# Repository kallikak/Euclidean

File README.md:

# Euclidean

This is the repository for the code for The EUCLIDEAN synthesiser. The main sketch is in the Euclid folder, but to build it some small changes need to be made to the Teensyduino environment.

- In order to use the Ensemble effect, the two files effect_ensemble.c and effect_ensemble.h need to be added to the audio library, and effect_ensemble.h added to the Audio.h header.

- The ST7735_t3 library is used for the LCD. The fonts I use are in the Fonts folder, and need to be added to the library if not already present.

- The other libraries needed are:
  - IntervalTimer
  - Bounce2mcp
  - Adafruit_MCP23017
  - MIDI
  - USBHost_t36
  - SD_t3.h
  - ADC (only needed if for some reason the pots are particularly noisy/jittery)

- You cannot use the default Audio Library GUI with the code from Euclid.ino because it doesn't recognise AudioEffectEnsemble.  The easiest change is to make it AudioEffectChorus  instead (and change AudioConnection patchCord60(chorus, 1, effectmixR, 1) to AudioConnection patchCord60(chorus, 0, effectmixR, 1)), but remember to change it back if you make changes and want to update.

- Compile with USB type set to Serial + MIDI + Audio, and no harm overclocking to 816MHz.

- Prebuilt hex files are provided for both Teensy 4.0 and Teensy 4.1.

A User Guide for the synthesizer is here: http://thewessens.net/Euclid/Docs/User/euclideaninfo.html

A Build Guide for the kit is here: http://thewessens.net/Euclid/Docs/Build/euclideanbuild.html

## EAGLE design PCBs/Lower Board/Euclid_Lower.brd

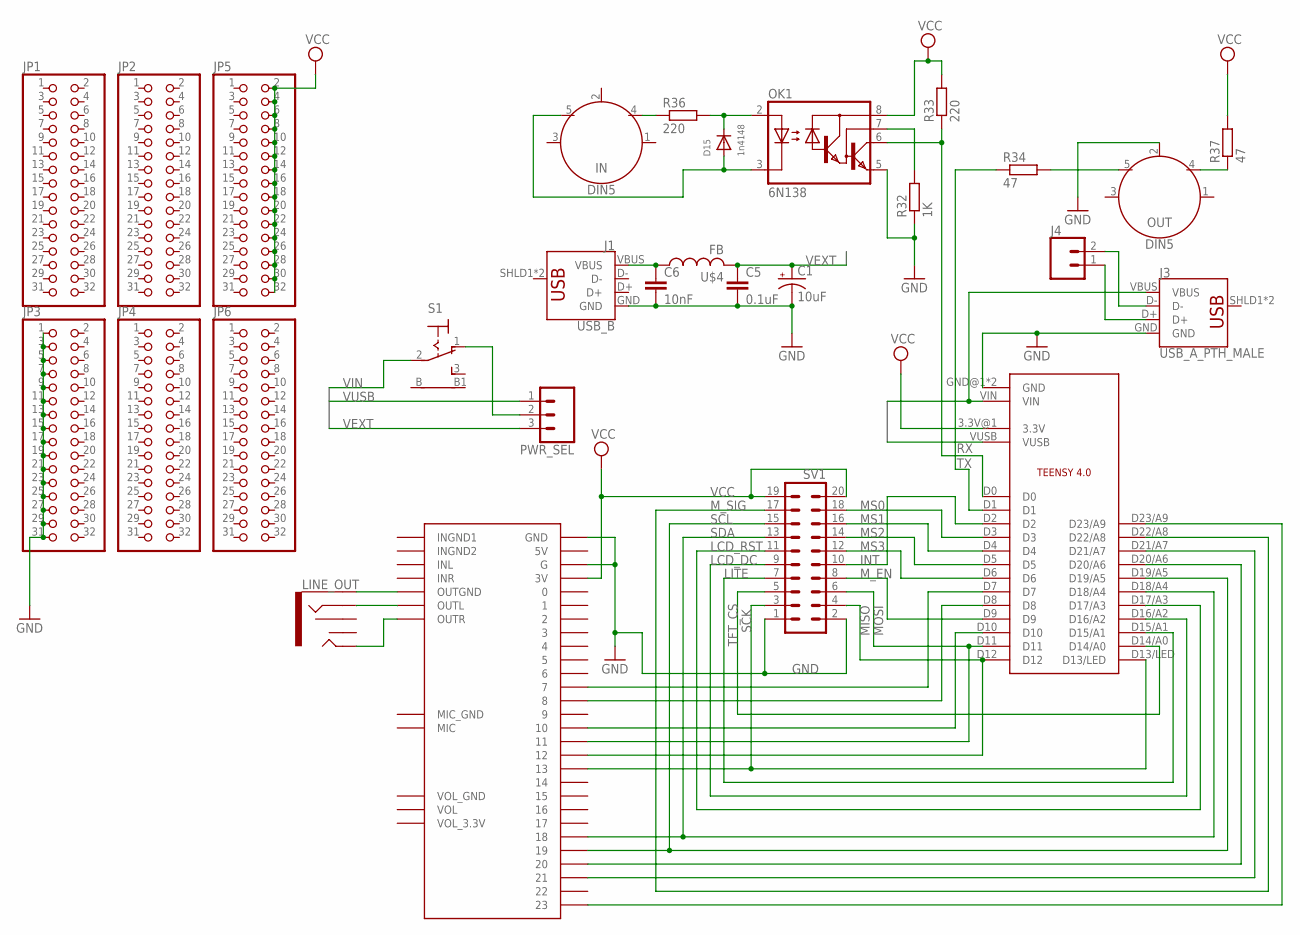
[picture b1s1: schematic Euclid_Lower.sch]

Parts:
C1: 10uF; TT5D6
C5: 0.1uF; C025-025X050
C6: 10nF; C025-025X050
D15: 1n4148; DO-1N4148
IN: DIN5; DIN5-RA-PTH
J1: USB_B; USB-B-NO-OVERHANG
J3: USB_A_PTH_MALE; USB-A-H
J4: CONN_02; 1X02
JP1, JP2, JP3, JP4, JP5, JP6: PINHD-2X16; 2X16
LINE_OUT: AUDIO_JACK_3.5MM_KIT; AUDIO-JACK-KIT
OK1: 6N138; DIL08
OUT: DIN5; DIN5-RA-PTH
PWR_SEL: 455-1750-1-ND; 1X03
R32: 1K; 0207/10
R33, R36: 220; 0207/10
R34, R37: 47; 0207/10
S1: 9070-1W
SV1: MA10-2
U$1: TEENSY4.0_SIMPLE
U$3: AUDIOSHIELD
U$4: FB

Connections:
D+: J3.D+, J4.1
D-: J3.D-, J4.2
GND: C1.-, C5.2, C6.2, J1.GND, J3.GND, JP3.1, JP3.3, JP3.5, JP3.7, JP3.9, JP3.11, JP3.13, JP3.15, JP3.17, JP3.19, JP3.21, JP3.23, JP3.25, JP3.27, JP3.29, JP3.31, OK1.5 (GND), OUT.2, R32.1, SV1.1, SV1.2, U$1.GND@1 (GND), U$1.GND@2 (GND), U$3.G, U$3.GND
INT: SV1.10, U$1.D2
LCD_DC: SV1.9, U$1.D16/A2
LCD_RST: SV1.11, U$1.D17/A3
LITE: SV1.7, U$1.D15/A1
MISO: SV1.4, U$1.D12, U$3.12
MOSI: SV1.6, U$1.D11, U$3.11
MS0: SV1.18, U$1.D3
MS1: SV1.16, U$1.D4
MS2: SV1.14, U$1.D5
MS3: SV1.12, U$1.D6
M_EN: SV1.8, U$1.D9
M_SIG: SV1.17, U$1.D22/A8
unnamed: U$1.D20/A6, U$3.20
unnamed: U$1.D21/A7, U$3.21
unnamed: U$1.D23/A9, U$3.23
unnamed: U$1.D10, U$3.10
unnamed: U$1.D7, U$3.7
unnamed: U$1.D8, U$3.8
unnamed: PWR_SEL.2, S1.1 (O)
unnamed: OUT.5, R34.2
unnamed: OK1.7 (VB), R32.2
unnamed: D15.A, IN.5, OK1.3 (C)
unnamed: D15.C, OK1.2 (A), R36.2
unnamed: IN.4, R36.1
unnamed: LINE_OUT.SLEEVE, U$3.OUTGND
unnamed: C6.1, J1.VBUS, U$4.P$1 (1)
unnamed: OUT.4, R37.1
unnamed: LINE_OUT.RING, U$3.OUTL
unnamed: LINE_OUT.TIP, U$3.OUTR
RX: OK1.6 (VO), R33.1, U$1.D0
SCK: SV1.3, U$1.D13/LED, U$3.13
SCL: SV1.15, U$1.D19/A5, U$3.19
SDA: SV1.13, U$1.D18/A4, U$3.18
TFT_CS: SV1.5, U$1.D14/A0
TX: R34.1, U$1.D1
VCC: JP5.2, JP5.4, JP5.6, JP5.8, JP5.10, JP5.12, JP5.14, JP5.16, JP5.18, JP5.20, JP5.22, JP5.24, JP5.26, JP5.28, JP5.30, JP5.32, OK1.8 (VCC), R33.2, R37.2, SV1.19, SV1.20, U$1.3.3V@1 (3.3V), U$3.3V
VEXT: C1.+, C5.1, PWR_SEL.3, U$4.P$2 (2)
VIN: J3.VBUS, S1.2, U$1.VIN
VUSB: PWR_SEL.1, U$1.VUSB

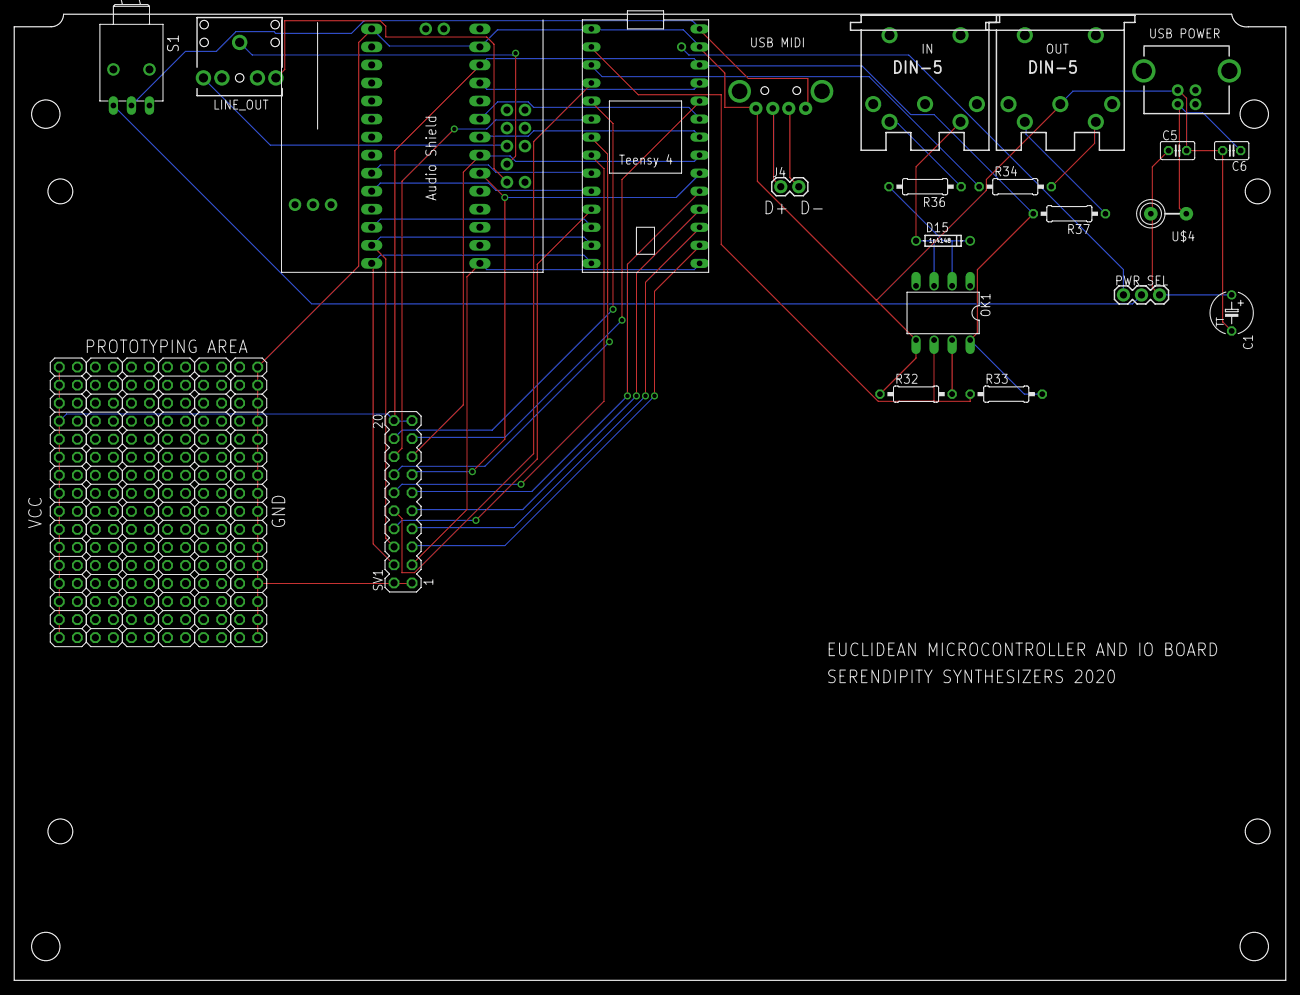
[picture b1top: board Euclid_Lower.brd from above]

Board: 2 copper layers, 179.1 x 136.1 mm, 28 parts (1 on the bottom side), 42 nets.

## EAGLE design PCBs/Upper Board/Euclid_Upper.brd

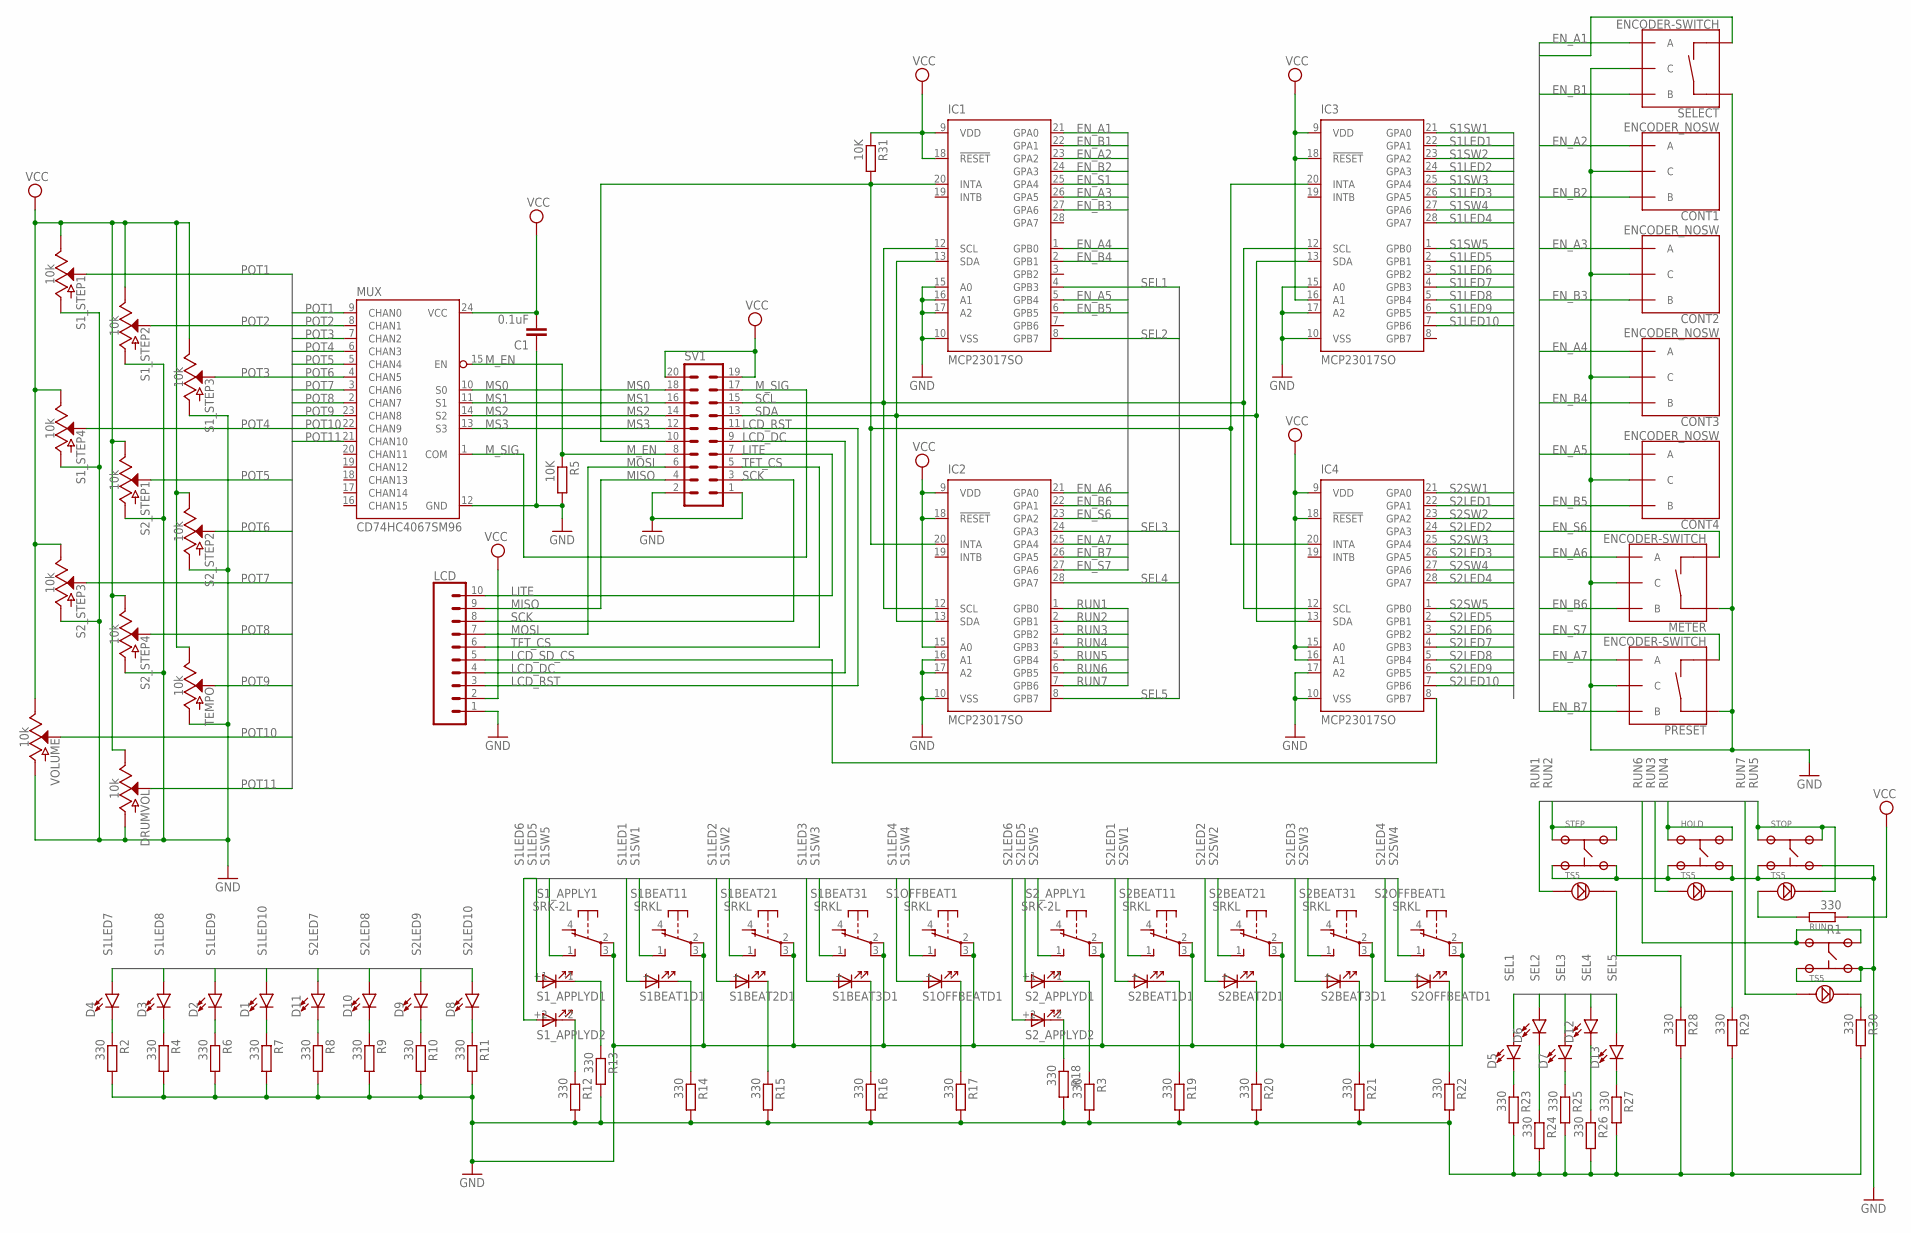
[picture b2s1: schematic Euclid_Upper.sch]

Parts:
C1: 0.1uF; C0603
CONT1, CONT2, CONT3, CONT4: ENCODER_NOSW
D1, D2, D3, D4, D5, D6, D7, D8, D9, D10, D11, D12, D13: LED3MM; LED_3MM
DRUMVOL: 10k; POT-PTH-ALPS
HOLD: TS5
IC1, IC2, IC3, IC4: MCP23017SO; SO28W
LCD: CONN_10"; 1X10
METER: ENCODER-SWITCH; ROTARY_ENC_PLAIN
MUX: CD74HC4067SM96; SSOP24
PRESET: ENCODER-SWITCH; ROTARY_ENC_PLAIN
R1, R2, R3, R4, R6, R7, R8, R9, R10, R11, R12, R13, R14, R15, R16, R17, R18, R19, R20, R21, R22, R23, R24, R25, R26, R27, R28, R29, R30: 330; R0603
R5, R31: 10K; R0603
RUN: TS5
S1BEAT1, S1BEAT2, S1BEAT3, S1OFFBEAT, S2BEAT1, S2BEAT2, S2BEAT3, S2OFFBEAT: SRKL
S1_APPLY, S2_APPLY: SRK-2L; SRK2L
S1_STEP1, S1_STEP2, S1_STEP3, S1_STEP4, S2_STEP1, S2_STEP2, S2_STEP3, S2_STEP4: 10k; POT-PTH-ALPS
SELECT: ENCODER-SWITCH; ROTARY_ENC_PLAIN
STEP: TS5
STOP: TS5
SV1: MA10-2
TEMPO: 10k; POT-PTH-ALPS
VOLUME: 10k; POT-PTH-ALPS

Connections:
EN_A1: IC1.21 (GPA0), SELECT.A
EN_A2: CONT1.A, IC1.23 (GPA2)
EN_A3: CONT2.A, IC1.26 (GPA5)
EN_A4: CONT3.A, IC1.1 (GPB0)
EN_A5: CONT4.A, IC1.5 (GPB4)
EN_A6: IC2.21 (GPA0), METER.A
EN_A7: IC2.25 (GPA4), PRESET.A
EN_B1: IC1.22 (GPA1), SELECT.B
EN_B2: CONT1.B, IC1.24 (GPA3)
EN_B3: CONT2.B, IC1.27 (GPA6)
EN_B4: CONT3.B, IC1.2 (GPB1)
EN_B5: CONT4.B, IC1.6 (GPB5)
EN_B6: IC2.22 (GPA1), METER.B
EN_B7: IC2.26 (GPA5), PRESET.B
EN_S1: IC1.25 (GPA4), SELECT.SW-
EN_S6: IC2.23 (GPA2), METER.SW-
EN_S7: IC2.27 (GPA6), PRESET.SW-
GND: C1.1, CONT1.C, CONT2.C, CONT3.C, CONT4.C, DRUMVOL.P$3 (A), HOLD.3, HOLD.4, IC1.10 (VSS), IC1.15 (A0), IC1.16 (A1), IC1.17 (A2), IC2.10 (VSS), IC2.16 (A1), IC2.17 (A2), IC3.10 (VSS), IC3.15 (A0), IC3.17 (A2), IC4.10 (VSS), IC4.17 (A2), LCD.1, METER.C, METER.SW+, MUX.12 (GND), PRESET.C, PRESET.SW+, R2.2, R3.2, R4.2, R5.2, R6.2, R7.2, R8.2, R9.2, R10.2, R11.2, R12.2, R13.2, R14.2, R15.2, R16.2, R17.2, R18.2, R19.2, R20.2, R21.2, R22.2, R23.2, R24.2, R25.2, R26.2, R27.2, R28.2, R29.2, R30.2, RUN.3, RUN.4, S1BEAT1.2, S1BEAT1.3, S1BEAT2.2, S1BEAT2.3, S1BEAT3.2, S1BEAT3.3, S1OFFBEAT.2, S1OFFBEAT.3, S1_APPLY.2, S1_APPLY.3, S1_STEP1.P$3 (A), S1_STEP2.P$3 (A), S1_STEP3.P$3 (A), S1_STEP4.P$3 (A), S2BEAT1.2, S2BEAT1.3, S2BEAT2.2, S2BEAT2.3, S2BEAT3.2, S2BEAT3.3, S2OFFBEAT.2, S2OFFBEAT.3, S2_APPLY.2, S2_APPLY.3, S2_STEP1.P$3 (A), S2_STEP2.P$3 (A), S2_STEP3.P$3 (A), S2_STEP4.P$3 (A), SELECT.C, SELECT.SW+, STEP.3, STEP.4, STOP.3, STOP.4, SV1.1, SV1.2, TEMPO.P$3 (A), VOLUME.P$3 (A)
LCD_DC: LCD.4, SV1.9
LCD_RST: LCD.3, SV1.11
LCD_SD_CS: IC4.8 (GPB7), LCD.5
LITE: LCD.10, SV1.7
MISO: LCD.9, SV1.4
MOSI: LCD.7, SV1.6
MS0: MUX.10 (S0), SV1.18
MS1: MUX.11 (S1), SV1.16
MS2: MUX.14 (S2), SV1.14
MS3: MUX.13 (S3), SV1.12
M_EN: MUX.15 (EN), R5.1, SV1.8
M_SIG: MUX.1 (COM), SV1.17
unnamed: IC1.20 (INTA), IC2.20 (INTA), IC3.20 (INTA), IC4.20 (INTA), R31.2, SV1.10
unnamed: R12.1, S1_APPLY.-2 (C)
unnamed: D8.K (C), R11.1
unnamed: R13.1, S1_APPLY.-1 (C)
unnamed: R14.1, S1BEAT1.- (C)
unnamed: R15.1, S1BEAT2.- (C)
unnamed: R16.1, S1BEAT3.- (C)
unnamed: R17.1, S1OFFBEAT.- (C)
unnamed: D9.K (C), R10.1
unnamed: D10.K (C), R9.1
unnamed: D11.K (C), R8.1
unnamed: R18.1, S2_APPLY.-2 (C)
unnamed: D1.K (C), R7.1
unnamed: D3.K (C), R4.1
unnamed: D4.K (C), R2.1
unnamed: D2.K (C), R6.1
unnamed: R21.1, S2BEAT3.- (C)
unnamed: R20.1, S2BEAT2.- (C)
unnamed: D5.K (C), R23.1
unnamed: R3.1, S2_APPLY.-1 (C)
unnamed: R19.1, S2BEAT1.- (C)
unnamed: D6.K (C), R24.1
unnamed: D7.K (C), R25.1
unnamed: R22.1, S2OFFBEAT.- (C)
unnamed: R30.1, RUN.5
unnamed: R28.1, STEP.5
unnamed: D12.K (C), R26.1
unnamed: R1.2, STOP.6
unnamed: HOLD.5, R29.1
unnamed: D13.K (C), R27.1
POT1: MUX.9 (CHAN0), S1_STEP1.P$2 (S)
POT2: MUX.8 (CHAN1), S1_STEP2.P$2 (S)
POT3: MUX.7 (CHAN2), S1_STEP3.P$2 (S)
POT4: MUX.6 (CHAN3), S1_STEP4.P$2 (S)
POT5: MUX.5 (CHAN4), S2_STEP1.P$2 (S)
POT6: MUX.4 (CHAN5), S2_STEP2.P$2 (S)
POT7: MUX.3 (CHAN6), S2_STEP3.P$2 (S)
POT8: MUX.2 (CHAN7), S2_STEP4.P$2 (S)
POT9: MUX.23 (CHAN8), TEMPO.P$2 (S)
POT10: MUX.22 (CHAN9), VOLUME.P$2 (S)
POT11: DRUMVOL.P$2 (S), MUX.21 (CHAN10)
RUN1: IC2.1 (GPB0), STEP.6
RUN2: IC2.2 (GPB1), STEP.1, STEP.2
RUN3: HOLD.6, IC2.3 (GPB2)
RUN4: HOLD.1, HOLD.2, IC2.4 (GPB3)
RUN5: IC2.5 (GPB4), STOP.1, STOP.2, STOP.5
RUN6: IC2.6 (GPB5), RUN.1, RUN.2
RUN7: IC2.7 (GPB6), RUN.6
S1LED1: IC3.22 (GPA1), S1BEAT1.+ (A)
S1LED2: IC3.24 (GPA3), S1BEAT2.+ (A)
S1LED3: IC3.26 (GPA5), S1BEAT3.+ (A)
S1LED4: IC3.28 (GPA7), S1OFFBEAT.+ (A)
S1LED5: IC3.2 (GPB1), S1_APPLY.+1 (A)
S1LED6: IC3.3 (GPB2), S1_APPLY.+2 (A)
S1LED7: D4.A, IC3.4 (GPB3)
S1LED8: D3.A, IC3.5 (GPB4)
S1LED9: D2.A, IC3.6 (GPB5)
S1LED10: D1.A, IC3.7 (GPB6)
S1SW1: IC3.21 (GPA0), S1BEAT1.1 (S)
S1SW2: IC3.23 (GPA2), S1BEAT2.1 (S)
S1SW3: IC3.25 (GPA4), S1BEAT3.1 (S)
S1SW4: IC3.27 (GPA6), S1OFFBEAT.1 (S)
S1SW5: IC3.1 (GPB0), S1_APPLY.1 (S)
S2LED1: IC4.22 (GPA1), S2BEAT1.+ (A)
S2LED2: IC4.24 (GPA3), S2BEAT2.+ (A)
S2LED3: IC4.26 (GPA5), S2BEAT3.+ (A)
S2LED4: IC4.28 (GPA7), S2OFFBEAT.+ (A)
S2LED5: IC4.2 (GPB1), S2_APPLY.+1 (A)
S2LED6: IC4.3 (GPB2), S2_APPLY.+2 (A)
S2LED7: D11.A, IC4.4 (GPB3)
S2LED8: D10.A, IC4.5 (GPB4)
S2LED9: D9.A, IC4.6 (GPB5)
S2LED10: D8.A, IC4.7 (GPB6)
S2SW1: IC4.21 (GPA0), S2BEAT1.1 (S)
S2SW2: IC4.23 (GPA2), S2BEAT2.1 (S)
S2SW3: IC4.25 (GPA4), S2BEAT3.1 (S)
S2SW4: IC4.27 (GPA6), S2OFFBEAT.1 (S)
S2SW5: IC4.1 (GPB0), S2_APPLY.1 (S)
SCK: LCD.8, SV1.3
SCL: IC1.12 (SCL), IC2.12 (SCL), IC3.12 (SCL), IC4.12 (SCL), SV1.15
SDA: IC1.13 (SDA), IC2.13 (SDA), IC3.13 (SDA), IC4.13 (SDA), SV1.13
SEL1: D5.A, IC1.4 (GPB3)
SEL2: D6.A, IC1.8 (GPB7)
SEL3: D7.A, IC2.24 (GPA3)
SEL4: D12.A, IC2.28 (GPA7)
SEL5: D13.A, IC2.8 (GPB7)
TFT_CS: LCD.6, SV1.5
VCC: C1.2, DRUMVOL.P$1 (E), IC1.9 (VDD), IC1.18 (!RESET), IC2.9 (VDD), IC2.15 (A0), IC2.18 (!RESET), IC3.9 (VDD), IC3.16 (A1), IC3.18 (!RESET), IC4.9 (VDD), IC4.15 (A0), IC4.16 (A1), IC4.18 (!RESET), LCD.2, MUX.24 (VCC), R1.1, R31.1, S1_STEP1.P$1 (E), S1_STEP2.P$1 (E), S1_STEP3.P$1 (E), S1_STEP4.P$1 (E), S2_STEP1.P$1 (E), S2_STEP2.P$1 (E), S2_STEP3.P$1 (E), S2_STEP4.P$1 (E), SV1.19, SV1.20, TEMPO.P$1 (E), VOLUME.P$1 (E)

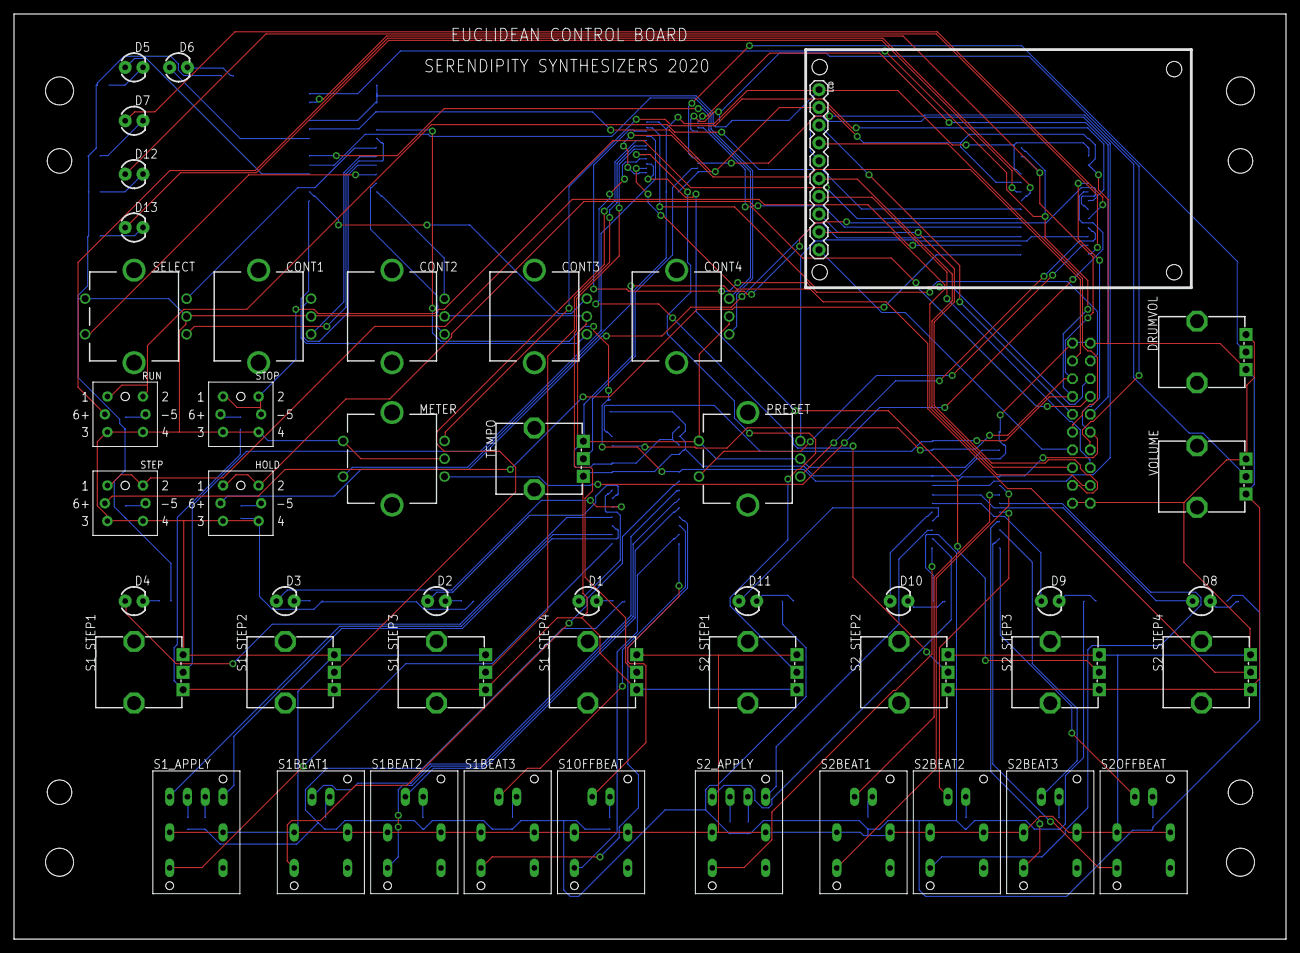
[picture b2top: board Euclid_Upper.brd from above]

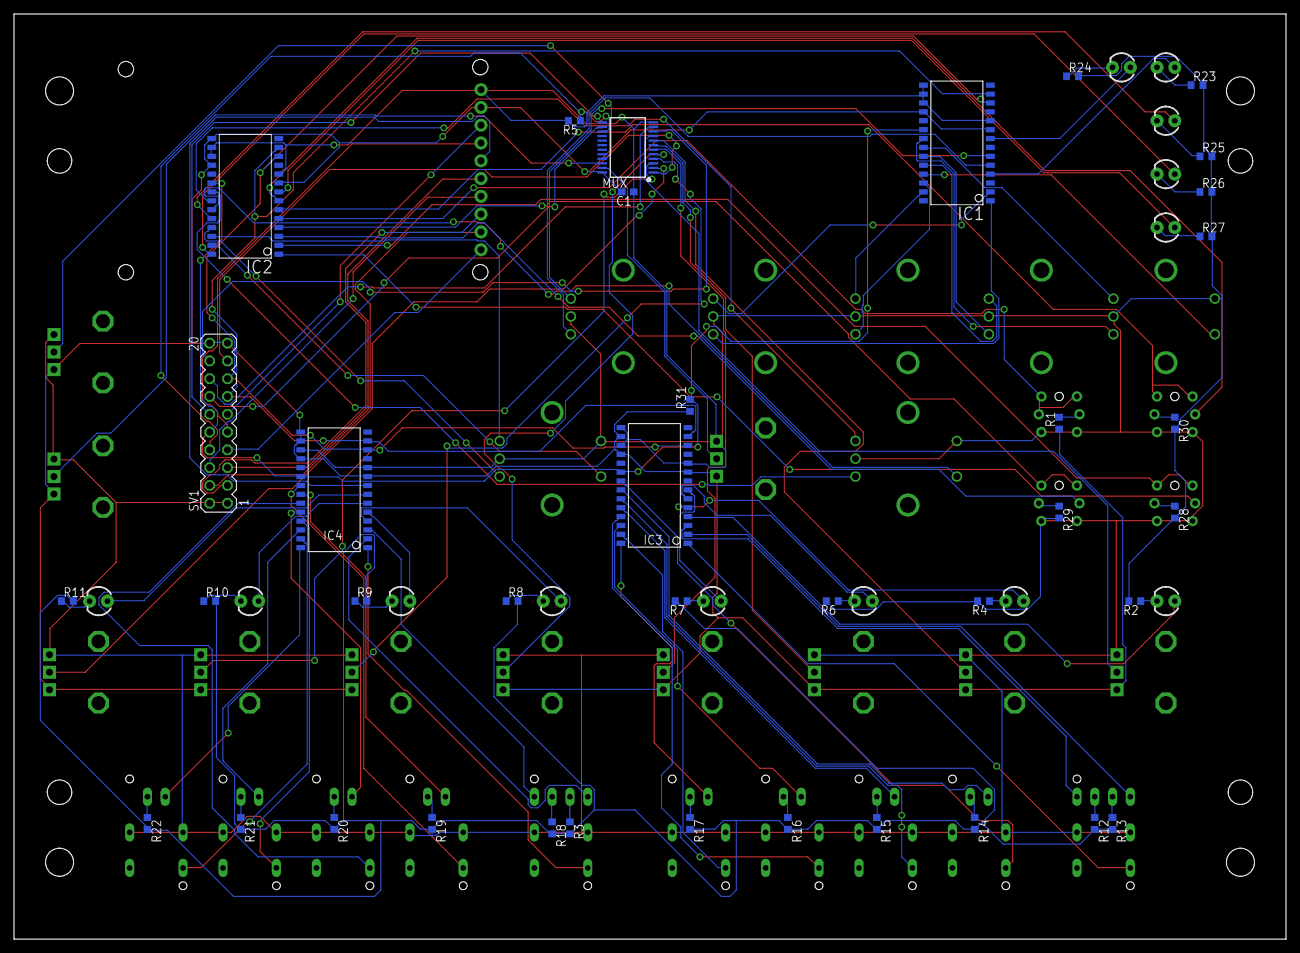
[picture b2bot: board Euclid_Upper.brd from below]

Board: 2 copper layers, 181.6 x 132.1 mm, 84 parts (38 on the bottom side), 118 nets.

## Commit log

2020-09-24 Initial upload
2020-09-29 Adjusted detune limits and fixed oscillator update bug
2020-09-29 Updated compiled firmware
2020-10-03 Fixed bug making pause too slow after changes to clocking
2020-10-04 Sequencer properly resets on run now
2020-10-04 Updated hex files
2020-10-04 MIDI all notes off to all 4 channels
2021-01-16 Added eagle files and berbers
2021-01-16 Added eagle files and gerbers
2021-02-13 External clock multiplier
2021-02-14 Improved external MIDI clocking functions
2021-02-16 Further fixes to external MIDI clock startup
2021-02-23 Compiled Firmware Update
2024-04-27 New version with sample file support

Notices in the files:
parts and their libraries:
SparkFun-Connectors: Licensing: CC v3.0 Share-Alike You are welcome to use this library for commercial purposes.
SparkFun-Resistors: Licensing: Creative Commons ShareAlike 4.0 International - https://creativecommons.org/licenses/by-sa/4.0
